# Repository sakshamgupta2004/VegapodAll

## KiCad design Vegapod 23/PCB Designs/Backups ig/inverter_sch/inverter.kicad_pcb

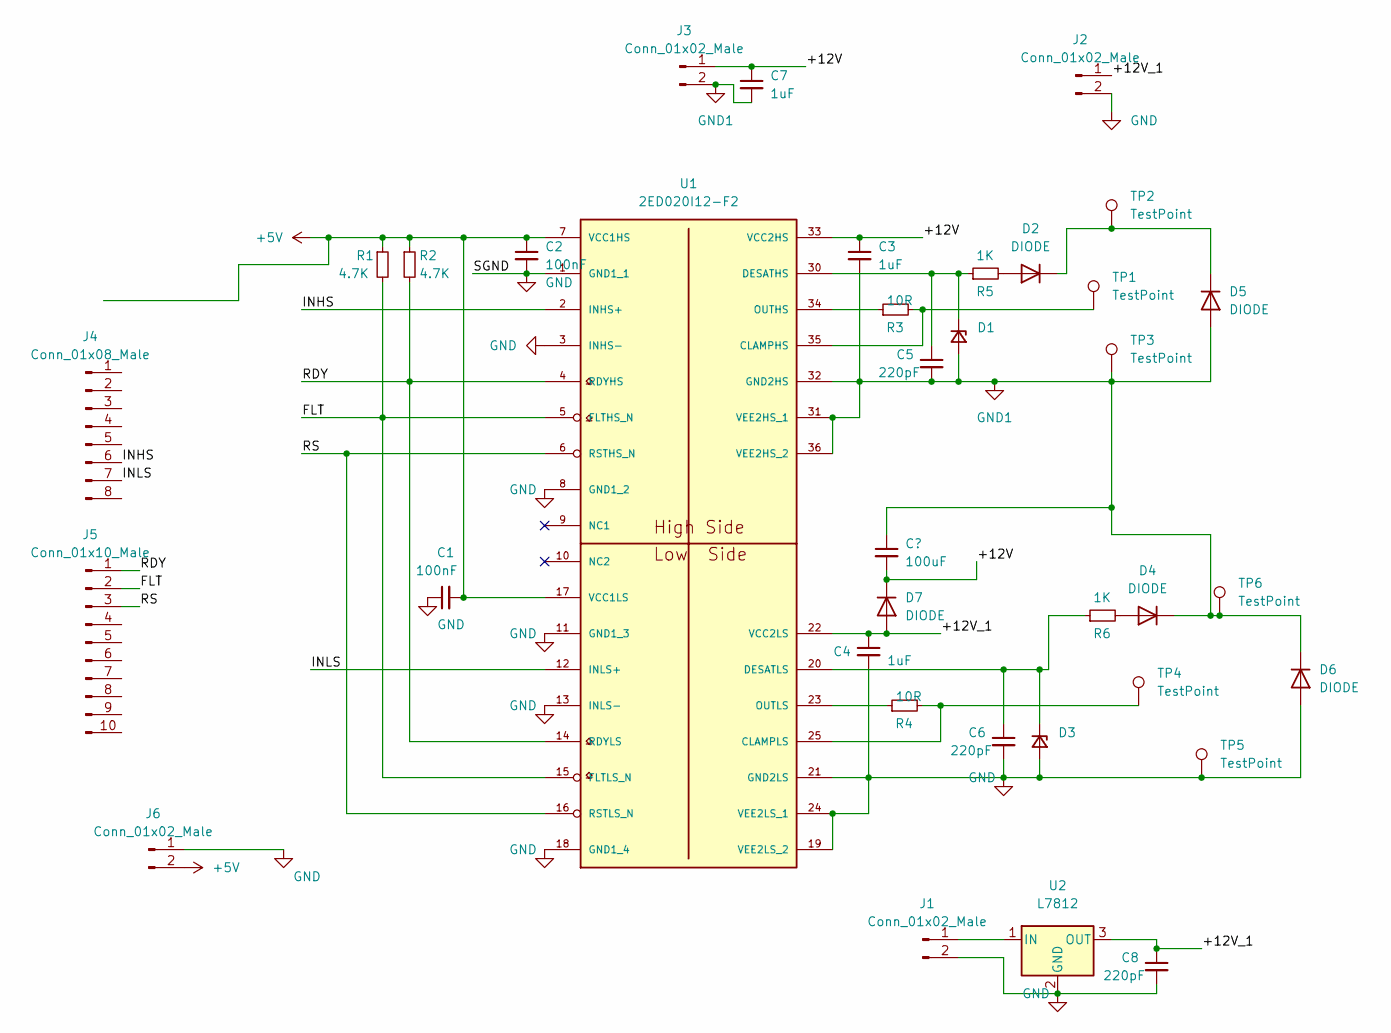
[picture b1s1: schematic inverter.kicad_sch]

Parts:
C1, C2: 100nF; CP_Radial_D14.0mm_P5.00mm
C3, C4, C7: 1uF; CP_Radial_D14.0mm_P5.00mm
C5, C6, C8: 220pF; CP_Radial_D14.0mm_P5.00mm
D1, D3: D_Zener_Small; D_DO-27_P15.24mm_Horizontal
D2, D4, D5, D6, D7: DIODE; D_DO-27_P15.24mm_Horizontal
J1, J2, J3: Conn_01x02_Male; PhoenixContact_MCV_1,5_2-G-5.08_1x02_P5.08mm_Vertical
J4: Conn_01x08_Male; PinHeader_1x08_P2.54mm_Vertical
J5: Conn_01x10_Male; PinHeader_1x10_P2.54mm_Vertical
J6: Conn_01x02_Male; PinHeader_1x02_P2.54mm_Vertical
R1, R2: 4.7K; R_Axial_DIN0411_L9.9mm_D3.6mm_P12.70mm_Horizontal
R3, R4: 10R; R_Axial_DIN0411_L9.9mm_D3.6mm_P12.70mm_Horizontal
R5, R6: 1K; R_Axial_DIN0411_L9.9mm_D3.6mm_P12.70mm_Horizontal
TP1, TP2, TP3, TP4, TP5, TP6: TestPoint; TestPoint_Pad_D4.0mm
U1: 2ED020I12-F2; SOP65P1030X265-36_32N-V
U2: L7812; TO-220-3_Vertical

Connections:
+5V: C1.2, C2.1, J6.2, R1.1, R2.1, U1.7 (VCC1HS), U1.17 (VCC1LS)
/+12V: C3.1, C7.1, D7.2 (K), J3.1, U1.33 (VCC2HS)
/+12V_1: C4.1, C8.1, D7.1 (A), J2.1, U1.22 (VCC2LS), U2.3 (OUT)
/FLT: J5.2, R1.2, U1.5 (FLTHS_N), U1.15 (FLTLS_N)
/INHS: J4.6, U1.2 (INHS+)
/INLS: J4.7, U1.12 (INLS+)
/RDY: J5.1, R2.2, U1.4 (RDYHS), U1.14 (RDYLS)
/RS: J5.3, U1.6 (RSTHS_N), U1.16 (RSTLS_N)
GND: C1.1, C2.2, C4.2, C6.2, C8.2, D3.2 (A), D6.1 (A), J1.2, J2.2, J6.1, TP5.1, U1.1 (GND1_1), U1.3 (INHS-), U1.8 (GND1_2), U1.11 (GND1_3), U1.13 (INLS-), U1.18 (GND1_4), U1.19 (VEE2LS_2), U1.21 (GND2LS), U1.24 (VEE2LS_1), U2.2 (GND)
GND1: C3.2, C5.2, C7.2, D1.2 (A), D4.2 (K), D5.1 (A), D6.2 (K), J3.2, TP3.1, TP6.1, U1.31 (VEE2HS_1), U1.32 (GND2HS), U1.36 (VEE2HS_2)
unnamed: C5.1, D1.1 (K), R5.1, U1.30 (DESATHS)
unnamed: C6.1, D3.1 (K), R6.1, U1.20 (DESATLS)
unnamed: D2.1 (A), R5.2
unnamed: D2.2 (K), D5.2 (K), TP2.1
unnamed: D4.1 (A), R6.2
unnamed: J1.1, U2.1 (IN)
unnamed: R3.1, U1.34 (OUTHS)
unnamed: R3.2, TP1.1, U1.35 (CLAMPHS)
unnamed: R4.1, U1.23 (OUTLS)
unnamed: R4.2, TP4.1, U1.25 (CLAMPLS)

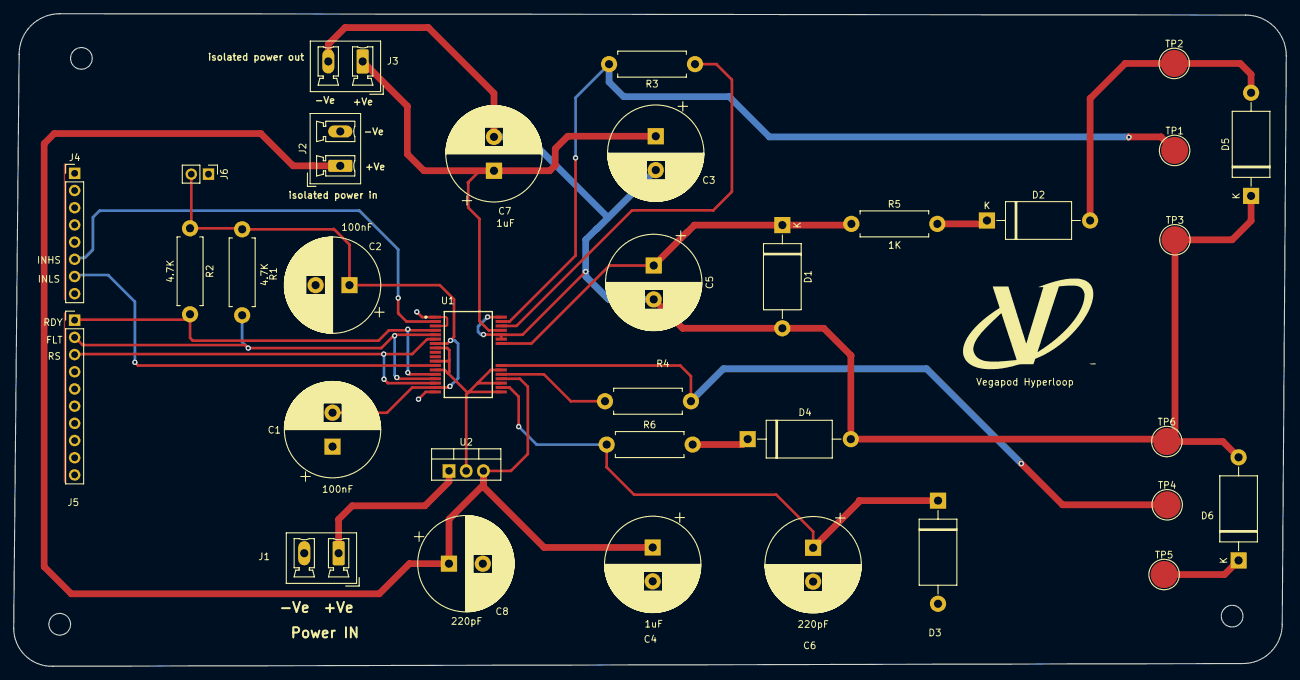
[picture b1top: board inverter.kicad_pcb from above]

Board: 2 copper layers, 188.0 x 96.4 mm, 34 parts (0 on the bottom side), 20 nets.

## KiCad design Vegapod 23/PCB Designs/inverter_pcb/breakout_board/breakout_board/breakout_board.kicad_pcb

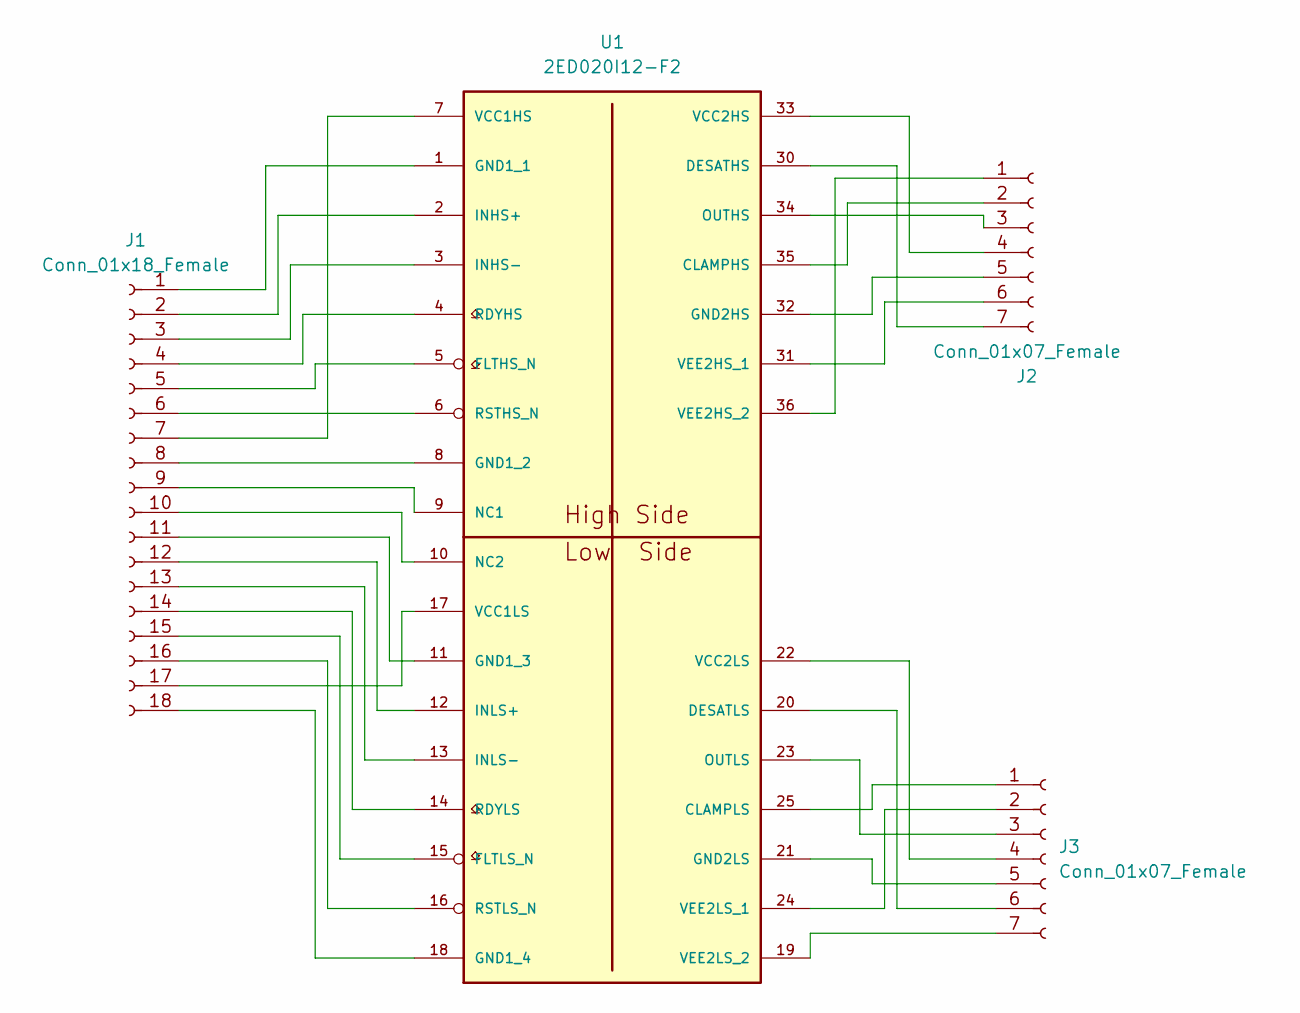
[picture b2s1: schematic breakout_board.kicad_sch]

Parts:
J1: Conn_01x18_Female; PinSocket_1x18_P2.54mm_Vertical
J2, J3: Conn_01x07_Female; PinSocket_1x07_P2.54mm_Vertical
U1: 2ED020I12-F2; SOP65P1030X265-36_32N-V

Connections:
unnamed: J1.1, U1.1 (GND1_1)
unnamed: J1.2, U1.2 (INHS+)
unnamed: J1.3, U1.3 (INHS-)
unnamed: J1.4, U1.4 (RDYHS)
unnamed: J1.5, U1.5 (FLTHS_N)
unnamed: J1.6, U1.6 (RSTHS_N)
unnamed: J1.7, U1.7 (VCC1HS)
unnamed: J1.8, U1.8 (GND1_2)
unnamed: J1.9, U1.9 (NC1)
unnamed: J1.10, U1.10 (NC2)
unnamed: J1.11, U1.11 (GND1_3)
unnamed: J1.12, U1.12 (INLS+)
unnamed: J1.13, U1.13 (INLS-)
unnamed: J1.14, U1.14 (RDYLS)
unnamed: J1.15, U1.15 (FLTLS_N)
unnamed: J1.16, U1.16 (RSTLS_N)
unnamed: J1.17, U1.17 (VCC1LS)
unnamed: J1.18, U1.18 (GND1_4)
unnamed: J2.1, U1.36 (VEE2HS_2)
unnamed: J2.2, U1.35 (CLAMPHS)
unnamed: J2.3, U1.34 (OUTHS)
unnamed: J2.4, U1.33 (VCC2HS)
unnamed: J2.5, U1.32 (GND2HS)
unnamed: J2.6, U1.31 (VEE2HS_1)
unnamed: J2.7, U1.30 (DESATHS)
unnamed: J3.1, U1.25 (CLAMPLS)
unnamed: J3.2, U1.24 (VEE2LS_1)
unnamed: J3.3, U1.23 (OUTLS)
unnamed: J3.4, U1.22 (VCC2LS)
unnamed: J3.5, U1.21 (GND2LS)
unnamed: J3.6, U1.20 (DESATLS)
unnamed: J3.7, U1.19 (VEE2LS_2)

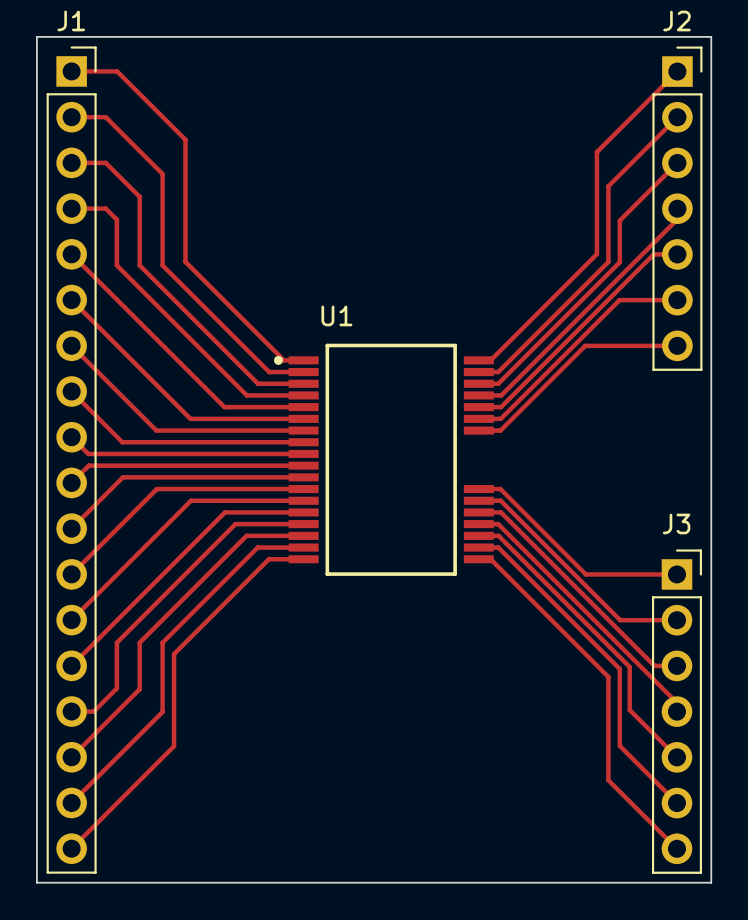
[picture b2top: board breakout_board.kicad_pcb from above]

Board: 2 copper layers, 37.5 x 47.0 mm, 4 parts (0 on the bottom side), 32 nets.

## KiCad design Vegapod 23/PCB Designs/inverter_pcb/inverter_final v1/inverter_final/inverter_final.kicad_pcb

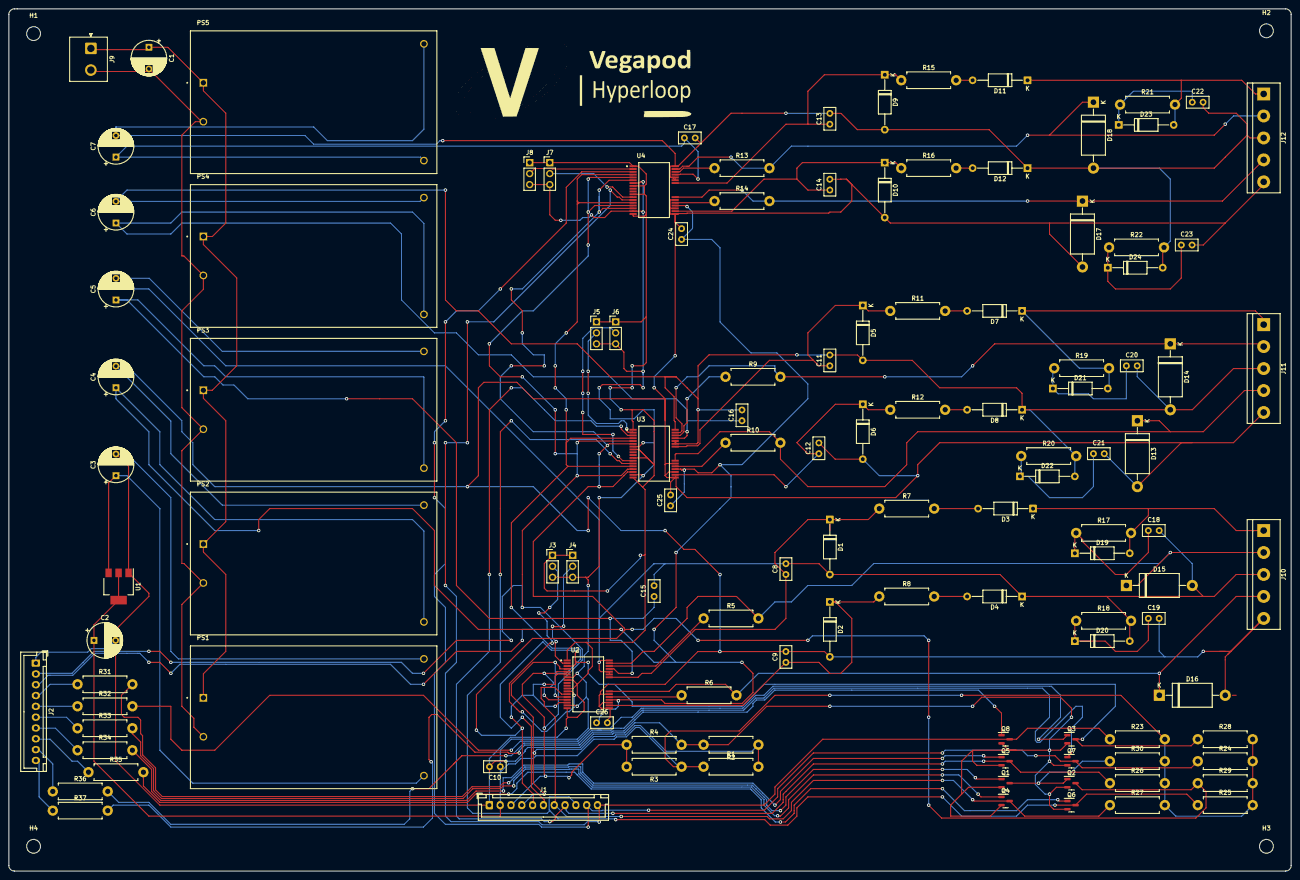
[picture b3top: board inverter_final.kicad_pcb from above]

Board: 2 copper layers, 296.5 x 199.4 mm, 120 parts (0 on the bottom side), 76 nets.

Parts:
C1: 100uF; CP_Radial_D8.0mm_P5.00mm
C2, C3, C4, C5, C6, C7: 1000uF; CP_Radial_D8.0mm_P5.00mm
C8, C9, C11, C12, C13, C14: 220pF; C_Disc_D5.0mm_W2.5mm_P2.50mm
C10, C15, C16, C17, C24, C25, C26: 100nF; C_Disc_D5.0mm_W2.5mm_P2.50mm
C18, C19, C20, C21, C22, C23: C_Snub; C_Disc_D5.0mm_W2.5mm_P2.50mm
D1, D2, D5, D6, D9, D10: D_Schottky; D_A-405_P12.70mm_Horizontal
D3, D4, D7, D8, D11, D12: 1N4007; D_A-405_P12.70mm_Horizontal
D13, D14, D15, D16, D17, D18: D_Zener; D_DO-201AE_P15.24mm_Horizontal
D19, D20, D21, D22, D23, D24: D_Snub; D_A-405_P12.70mm_Horizontal
H1, H2, H3, H4: MountingHole; MountingHole_3.2mm_M3
J1: Conn_01x11_Male; JST_XH_B11B-XH-A_1x11_P2.50mm_Vertical
J2: Conn_01x10_Male; JST_XH_B10B-XH-A_1x10_P2.50mm_Vertical
J3, J4, J5, J6, J7, J8: Conn_01x03_Male; PinHeader_1x03_P2.54mm_Vertical
J9: Conn_01x02_Male; JST_NV_B02P-NV_1x02_P5.00mm_Vertical
J10, J11, J12: Screw_Terminal_01x05; TerminalBlock_bornier-5_P5.08mm
PS1, PS2, PS3, PS4, PS5: HLK-20M05; CONV_HLK-20M05
Q1, Q2, Q3, Q4, Q5, Q6, Q7, Q8: MMBT3904; SOT-23
R1, R3: 3.3K; R_Axial_DIN0411_L9.9mm_D3.6mm_P12.70mm_Horizontal
R2, R4: 4.7K; R_Axial_DIN0411_L9.9mm_D3.6mm_P12.70mm_Horizontal
R5, R6, R9, R10, R13, R14: 10; R_Axial_DIN0411_L9.9mm_D3.6mm_P12.70mm_Horizontal
R7, R8, R11, R12, R15, R16, R23, R24, R25, R26, R27, R28, R29, R30, R31, R32, R33, R34, R35, R36, R37: 1K; R_Axial_DIN0411_L9.9mm_D3.6mm_P12.70mm_Horizontal
R17, R18, R19, R20, R21, R22: R_Snub; R_Axial_DIN0411_L9.9mm_D3.6mm_P12.70mm_Horizontal
U1: AMS1117-5.0; SOT-223-3_TabPin2
U2, U3, U4: 2ED020I12-F2; SOP65P1030X265-36_32N-V

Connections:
+5V: C2.1, C10.1, J1.2, J3.3, J4.3, J5.3, J6.3, J7.3, J8.3, R1.1, R3.1, R23.2, R24.2, R25.2, R26.2, R27.2, R28.2, R29.2, R30.2, U1.2 (VO), U2.7 (VCC1HS), U2.17 (VCC1LS), U3.7 (VCC1HS), U3.17 (VCC1LS), U4.7 (VCC1HS), U4.17 (VCC1LS)
+15V: C4.1, C24.1, C25.1, C26.1, PS2.4 (+VO), U2.22 (VCC2LS), U3.22 (VCC2LS), U4.22 (VCC2LS)
+BATT: C1.1, J9.1, PS1.1 (AC(L)), PS2.1 (AC(L)), PS3.1 (AC(L)), PS4.1 (AC(L)), PS5.1 (AC(L))
-BATT: C1.2, J9.2, PS1.2 (AC(N)), PS2.2 (AC(N)), PS3.2 (AC(N)), PS4.2 (AC(N)), PS5.2 (AC(N))
FLT: J1.3, J2.2, R3.2, R4.1, U2.5 (FLTHS_N), U2.15 (FLTLS_N), U3.5 (FLTHS_N), U3.15 (FLTLS_N), U4.5 (FLTHS_N), U4.15 (FLTLS_N)
GND: C4.2, C9.2, C12.2, C14.2, C19.2, C21.2, C23.2, C24.2, C25.2, C26.2, D2.2 (A), D6.2 (A), D10.2 (A), D13.2 (A), D16.2 (A), D17.2 (A), J10.5, J11.5, J12.5, PS2.3 (-VO), U2.19 (VEE2LS_2), U2.21 (GND2LS), U2.24 (VEE2LS_1), U3.19 (VEE2LS_2), U3.21 (GND2LS), U3.24 (VEE2LS_1), U4.19 (VEE2LS_2), U4.21 (GND2LS), U4.24 (VEE2LS_1)
GND1: C5.2, C8.2, C15.2, C18.2, D1.2 (A), D4.1 (K), D15.2 (A), D20.2 (A), J10.3, PS3.3 (-VO), R18.2, U2.31 (VEE2HS_1), U2.32 (GND2HS), U2.36 (VEE2HS_2)
GND2: C6.2, C11.2, C16.2, C20.2, D5.2 (A), D8.1 (K), D14.2 (A), D22.2 (A), J11.3, PS4.3 (-VO), R20.2, U3.31 (VEE2HS_1), U3.32 (GND2HS), U3.36 (VEE2HS_2)
GND3: C7.2, C13.2, C17.2, C22.2, D9.2 (A), D12.1 (K), D18.2 (A), D24.2 (A), J12.3, PS5.3 (-VO), R22.2, U4.31 (VEE2HS_1), U4.32 (GND2HS), U4.36 (VEE2HS_2)
GNDD: C2.2, C3.2, C10.2, J1.1, J2.1, J3.1, J4.1, J5.1, J6.1, J7.1, J8.1, PS1.3 (-VO), Q1.2 (E), Q2.2 (E), Q3.2 (E), Q4.2 (E), Q5.2 (E), Q6.2 (E), Q7.2 (E), Q8.2 (E), R2.2, R4.2, U1.1 (GND), U2.1 (GND1_1), U2.8 (GND1_2), U2.11 (GND1_3), U2.18 (GND1_4), U3.1 (GND1_1), U3.8 (GND1_2), U3.11 (GND1_3), U3.18 (GND1_4), U4.1 (GND1_1), U4.8 (GND1_2), U4.11 (GND1_3), U4.18 (GND1_4)
INHS1: J1.6, Q3.3 (C), R28.1, U2.3 (INHS-)
INHS2: J1.8, Q5.3 (C), R26.1, U3.3 (INHS-)
INHS3: J1.10, Q7.3 (C), R24.1, U4.3 (INHS-)
INLS1: J1.7, Q4.3 (C), R27.1, U2.13 (INLS-)
INLS2: J1.9, Q6.3 (C), R25.1, U3.13 (INLS-)
INLS3: J1.11, Q8.3 (C), R23.1, U4.13 (INLS-)
unnamed: C8.1, D1.1 (K), R7.1, U2.30 (DESATHS)
unnamed: C9.1, D2.1 (K), R8.1, U2.20 (DESATLS)
unnamed: C11.1, D5.1 (K), R11.1, U3.30 (DESATHS)
unnamed: C12.1, D6.1 (K), R12.1, U3.20 (DESATLS)
unnamed: C13.1, D9.1 (K), R15.1, U4.30 (DESATHS)
unnamed: C14.1, D10.1 (K), R16.1, U4.20 (DESATLS)
unnamed: C18.1, D19.1 (K), R17.1
unnamed: C19.1, D20.1 (K), R18.1
unnamed: C20.1, D21.1 (K), R19.1
unnamed: C21.1, D22.1 (K), R20.1
unnamed: C22.1, D23.1 (K), R21.1
unnamed: C23.1, D24.1 (K), R22.1
unnamed: D3.2 (A), R7.2
unnamed: D4.2 (A), R8.2
unnamed: D7.2 (A), R11.2
unnamed: D8.2 (A), R12.2
unnamed: D11.1 (K), D23.2 (A), J12.1, R21.2
unnamed: D11.2 (A), R15.2
unnamed: D12.2 (A), R16.2
unnamed: D13.1 (K), J11.4, R10.2, U3.25 (CLAMPLS)
unnamed: D14.1 (K), J11.2, R9.2, U3.35 (CLAMPHS)
unnamed: D15.1 (K), J10.2, R5.2, U2.35 (CLAMPHS)
unnamed: D16.1 (K), J10.4, R6.2, U2.25 (CLAMPLS)
unnamed: D17.1 (K), J12.4, R14.2, U4.25 (CLAMPLS)
unnamed: D18.1 (K), J12.2, R13.2, U4.35 (CLAMPHS)
unnamed: D3.1 (K), D19.2 (A), J10.1, R17.2
unnamed: D7.1 (K), D21.2 (A), J11.1, R19.2
unnamed: J2.4, R31.1
unnamed: J2.5, R32.1
unnamed: J2.6, R33.1
unnamed: J2.7, R34.1
unnamed: J2.8, R35.1
unnamed: J2.9, R36.1
unnamed: J2.10, R37.1
unnamed: J3.2, U2.12 (INLS+)
unnamed: J4.2, U2.2 (INHS+)
unnamed: J5.2, U3.2 (INHS+)
unnamed: J6.2, U3.12 (INLS+)
unnamed: J7.2, U4.12 (INLS+)
unnamed: J8.2, U4.2 (INHS+)
unnamed: Q1.1 (B), R31.2
unnamed: Q1.3 (C), Q2.1 (B), R30.1
unnamed: Q3.1 (B), R32.2
unnamed: Q4.1 (B), R33.2
unnamed: Q5.1 (B), R34.2
unnamed: Q6.1 (B), R35.2
unnamed: Q7.1 (B), R36.2
unnamed: Q8.1 (B), R37.2
unnamed: R5.1, U2.34 (OUTHS)
unnamed: R6.1, U2.23 (OUTLS)
unnamed: R9.1, U3.34 (OUTHS)
unnamed: R10.1, U3.23 (OUTLS)
unnamed: R13.1, U4.34 (OUTHS)
unnamed: R14.1, U4.23 (OUTLS)
RDY: J1.4, J2.3, R1.2, R2.1, U2.4 (RDYHS), U2.14 (RDYLS), U3.4 (RDYHS), U3.14 (RDYLS), U4.4 (RDYHS), U4.14 (RDYLS)
RST: J1.5, Q2.3 (C), R29.1, U2.6 (RSTHS_N), U2.16 (RSTLS_N), U3.6 (RSTHS_N), U3.16 (RSTLS_N), U4.6 (RSTHS_N), U4.16 (RSTLS_N)
VDD: C3.1, PS1.4 (+VO), U1.3 (VI)
VDrive1: C5.1, C15.1, PS3.4 (+VO), U2.33 (VCC2HS)
VDrive2: C6.1, C16.1, PS4.4 (+VO), U3.33 (VCC2HS)
VDrive3: C7.1, C17.1, PS5.4 (+VO), U4.33 (VCC2HS)

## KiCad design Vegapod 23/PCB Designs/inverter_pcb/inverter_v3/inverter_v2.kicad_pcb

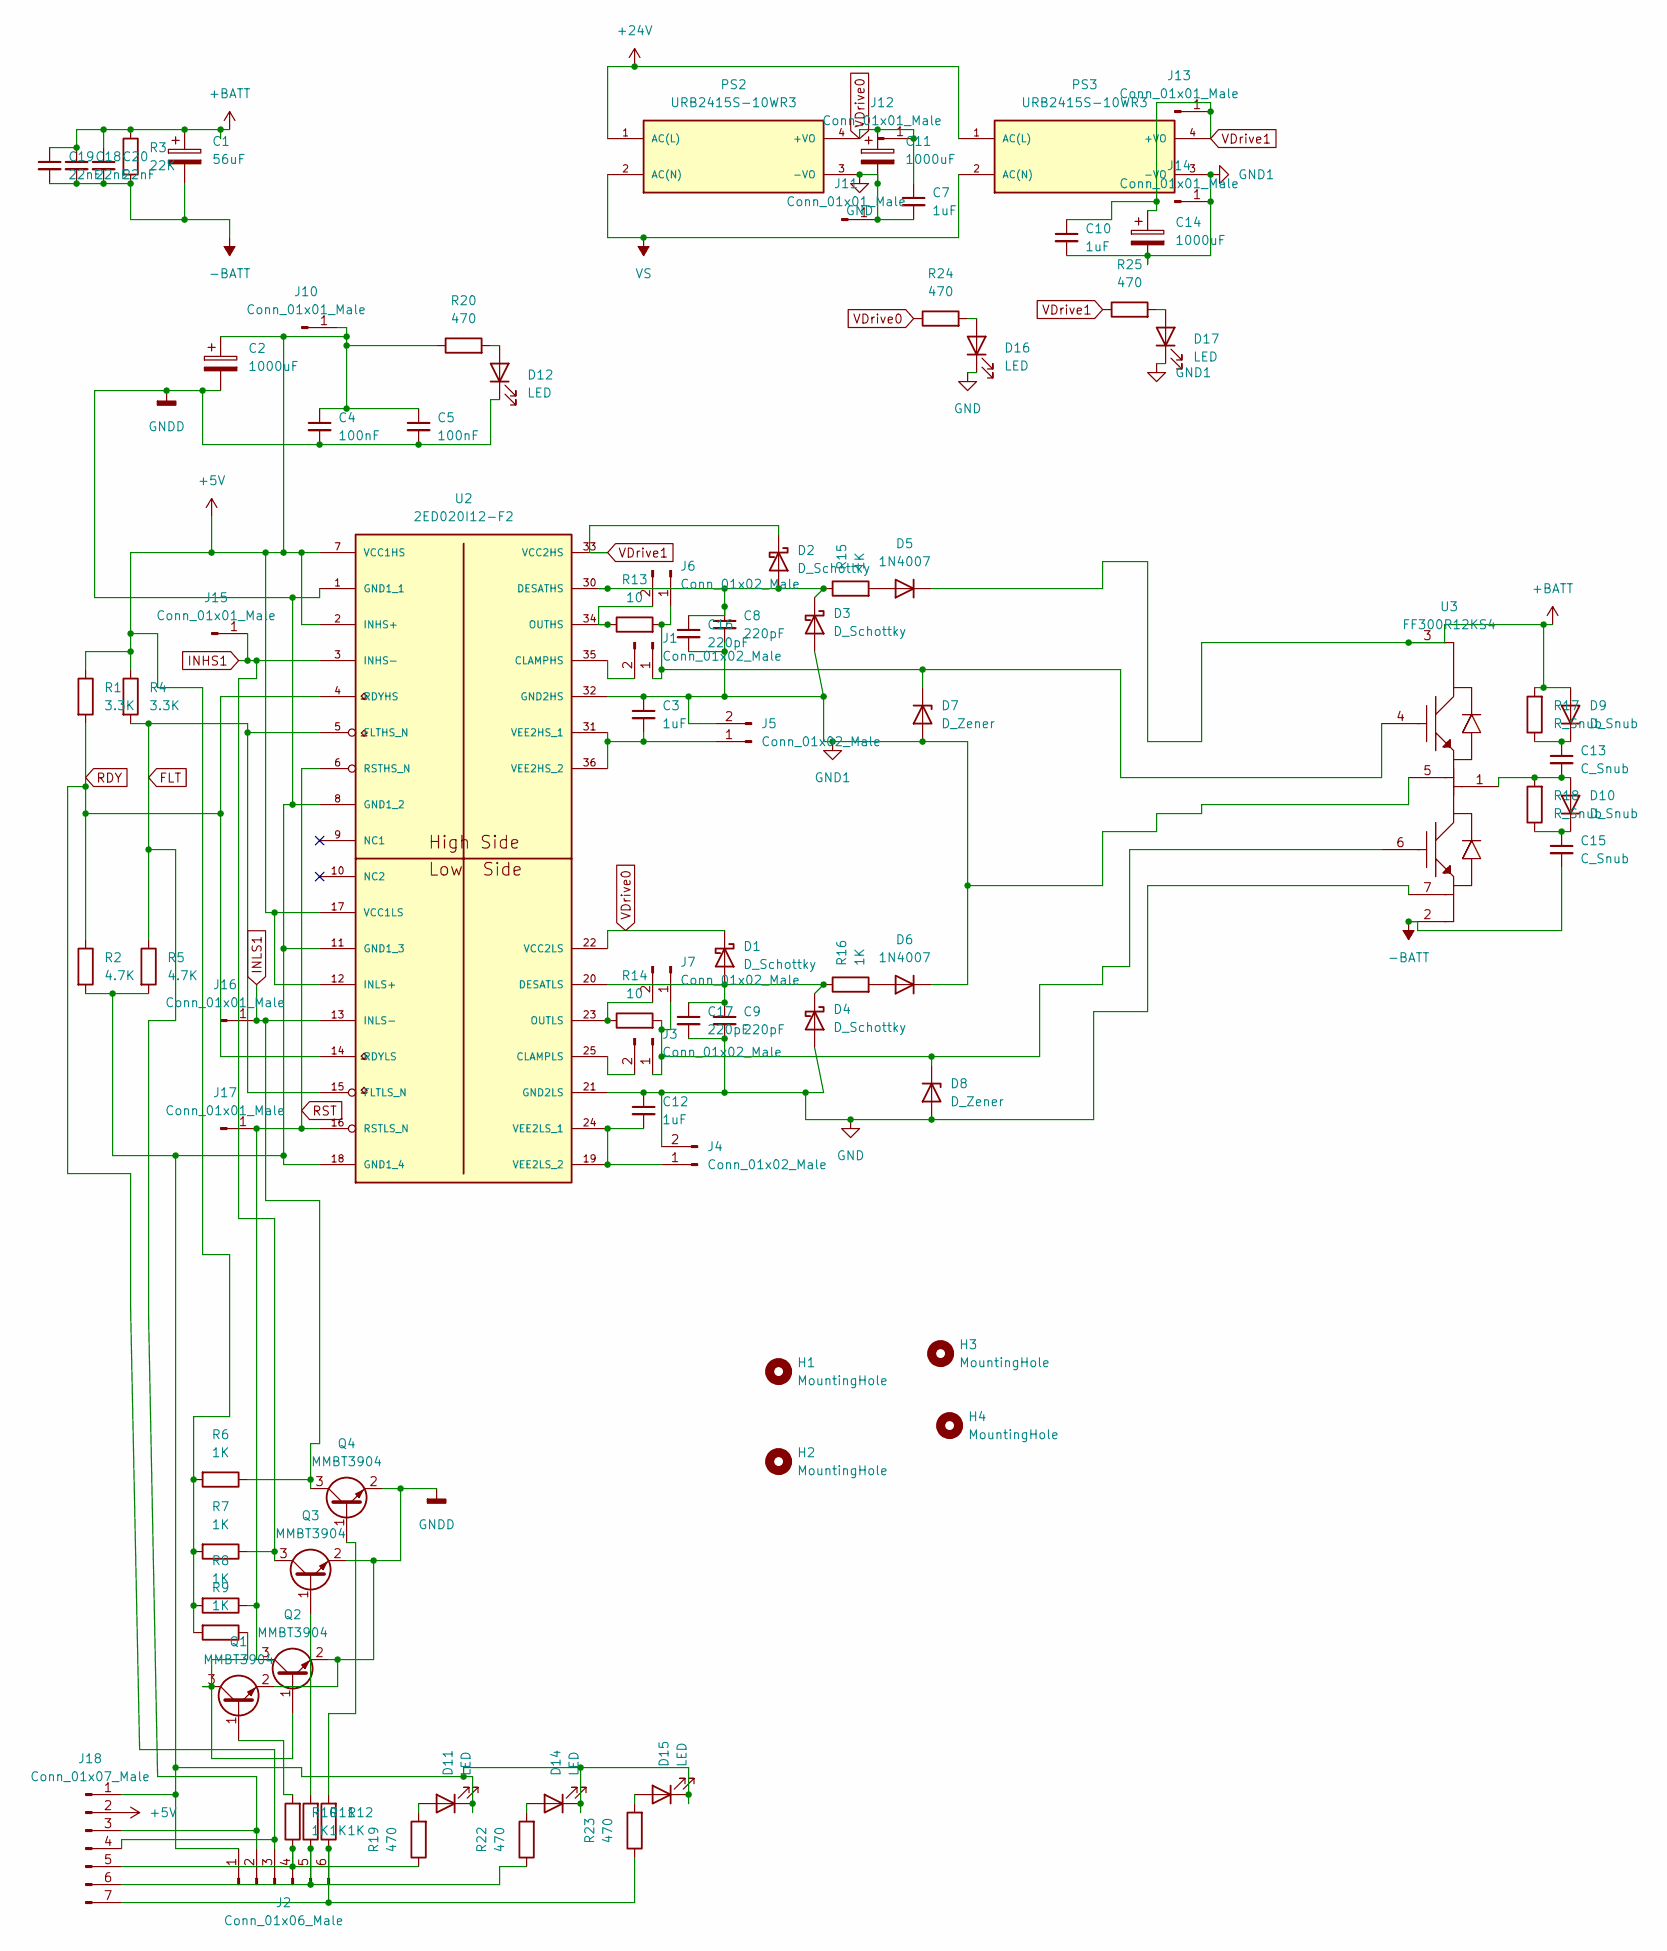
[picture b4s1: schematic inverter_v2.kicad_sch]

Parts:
C1: 56uF; CP_Radial_D16.0mm_P7.50mm
C2: 1000uF; CP_Elec_10x10.5
C3, C7, C10, C12: 1uF; C_1206_3216Metric_Pad1.33x1.80mm_HandSolder
C4, C5: 100nF; C_0603_1608Metric_Pad1.08x0.95mm_HandSolder
C8, C9, C16, C17: 220pF; C_0603_1608Metric_Pad1.08x0.95mm_HandSolder
C11, C14: 1000uF; CAP_EEEFK1E102AQ
C13, C15: C_Snub; C_Rect_L24.0mm_W8.3mm_P22.50mm_MKT
C18, C19, C20: 22nF; C_1206_3216Metric_Pad1.33x1.80mm_HandSolder
D1, D2, D3, D4: D_Schottky; D_SMA_Handsoldering
D5, D6: 1N4007; D_SMA_Handsoldering
D7, D8: D_Zener; D_SOD-123
D9, D10: D_Snub; D_DO-201AE_P15.24mm_Horizontal
D11, D12, D14, D15, D16, D17: LED; LED_0805_2012Metric_Pad1.15x1.40mm_HandSolder
H1, H2, H3, H4: MountingHole; MountingHole_3.2mm_M3
J1, J3, J4, J5, J6, J7: Conn_01x02_Male; PinHeader_1x02_P1.27mm_Vertical
J2: Conn_01x06_Male; JST_XH_B6B-XH-A_1x06_P2.50mm_Vertical
J10, J11, J12, J13, J14, J15, J16, J17: Conn_01x01_Male; PinHeader_1x01_P2.54mm_Vertical
J18: Conn_01x07_Male; JST_XH_B7B-XH-A_1x07_P2.50mm_Vertical
PS2, PS3: URB2415S-10WR3; CONV_HLK-20M05; PARTREV V1.3
Q1, Q2, Q3, Q4: MMBT3904; SOT-23
R1, R4: 3.3K; R_0603_1608Metric_Pad0.98x0.95mm_HandSolder
R2, R5: 4.7K; R_0603_1608Metric_Pad0.98x0.95mm_HandSolder
R3: 22K; R_1206_3216Metric_Pad1.30x1.75mm_HandSolder
R6, R7, R8, R9, R10, R11, R12, R15, R16: 1K; R_0603_1608Metric_Pad0.98x0.95mm_HandSolder
R13, R14: 10; R_1206_3216Metric_Pad1.30x1.75mm_HandSolder
R17, R18: R_Snub; R_Box_L26.0mm_W5.0mm_P20.00mm
R19, R20, R22, R23, R24, R25: 470; R_0603_1608Metric_Pad0.98x0.95mm_HandSolder
U2: 2ED020I12-F2; SOP65P1030X265-36_32N-V
U3: FF300R12KS4

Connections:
+5V: C2.1, C4.1, C5.1, J10.1, J18.2, R1.1, R4.1, R6.2, R7.2, R8.2, R9.2, R20.1, U2.2 (INHS+), U2.7 (VCC1HS), U2.12 (INLS+), U2.17 (VCC1LS); also elsewhere on the board
FLT: J2.2, J18.3, R4.2, R5.1, U2.5 (FLTHS_N), U2.15 (FLTLS_N)
GND: C7.2, C9.2, C11.2, C12.1, C17.2, D4.2 (A), D8.2 (A), D16.1 (K), J4.2, J11.1, PS2.3 (-VO), U2.21 (GND2LS), U3.7
GND1: C3.1, C8.2, C10.2, C14.2, C16.2, D3.2 (A), D6.1 (K), D7.2 (A), D17.1 (K), J5.2, J14.1, PS3.3 (-VO), U2.32 (GND2HS), U3.5
GNDD: C2.2, C4.2, C5.2, D11.1 (K), D12.1 (K), D14.1 (K), D15.1 (K), J2.1, J18.1, Q1.2 (E), Q2.2 (E), Q3.2 (E), Q4.2 (E), R2.2, R5.2, U2.1 (GND1_1), U2.8 (GND1_2), U2.11 (GND1_3), U2.18 (GND1_4); also elsewhere on the board
INHS1: J15.1, Q3.3 (C), R7.1, U2.3 (INHS-)
INLS1: J16.1, Q4.3 (C), R6.1, U2.13 (INLS-)
unnamed: C3.2, J5.1, U2.31 (VEE2HS_1), U2.36 (VEE2HS_2)
unnamed: C12.2, J4.1, U2.19 (VEE2LS_2), U2.24 (VEE2LS_1)
unnamed: C13.1, D9.1 (K), R17.1
unnamed: C13.2, D10.2 (A), R18.2, U3.1
unnamed: C15.1, D10.1 (K), R18.1
unnamed: C8.1, C16.1, D2.2 (A), D3.1 (K), R15.1, U2.30 (DESATHS)
unnamed: C9.1, C17.1, D1.2 (A), D4.1 (K), R16.1, U2.20 (DESATLS)
unnamed: D5.2 (A), R15.2
unnamed: D6.2 (A), R16.2
unnamed: D7.1 (K), J1.1, J6.1, R13.2, U3.4
unnamed: D8.1 (K), J3.1, J7.1, R14.2, U3.6
unnamed: D11.2 (A), R19.2
unnamed: D12.2 (A), R20.2
unnamed: D14.2 (A), R22.2
unnamed: D15.2 (A), R23.2
unnamed: D16.2 (A), R24.2
unnamed: D17.2 (A), R25.2
unnamed: J1.2, U2.35 (CLAMPHS)
unnamed: J3.2, U2.25 (CLAMPLS)
unnamed: J6.2, R13.1, U2.34 (OUTHS)
unnamed: J7.2, R14.1, U2.23 (OUTLS)
unnamed: J2.4, J18.5, R10.1, R19.1
unnamed: J2.5, J18.6, R11.1, R22.1
unnamed: J2.6, J18.7, R12.1, R23.1
unnamed: Q1.1 (B), R10.2
unnamed: Q1.3 (C), Q2.1 (B), R9.1
unnamed: Q3.1 (B), R11.2
unnamed: Q4.1 (B), R12.2
RDY: J2.3, J18.4, R1.2, R2.1, U2.4 (RDYHS), U2.14 (RDYLS)
RST: J17.1, Q2.3 (C), R8.1, U2.6 (RSTHS_N), U2.16 (RSTLS_N)
VDrive0: C7.1, C11.1, D1.1 (K), J12.1, PS2.4 (+VO), R24.1, U2.22 (VCC2LS)
VDrive1: C10.1, C14.1, D2.1 (K), J13.1, PS3.4 (+VO), R25.1, U2.33 (VCC2HS)

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
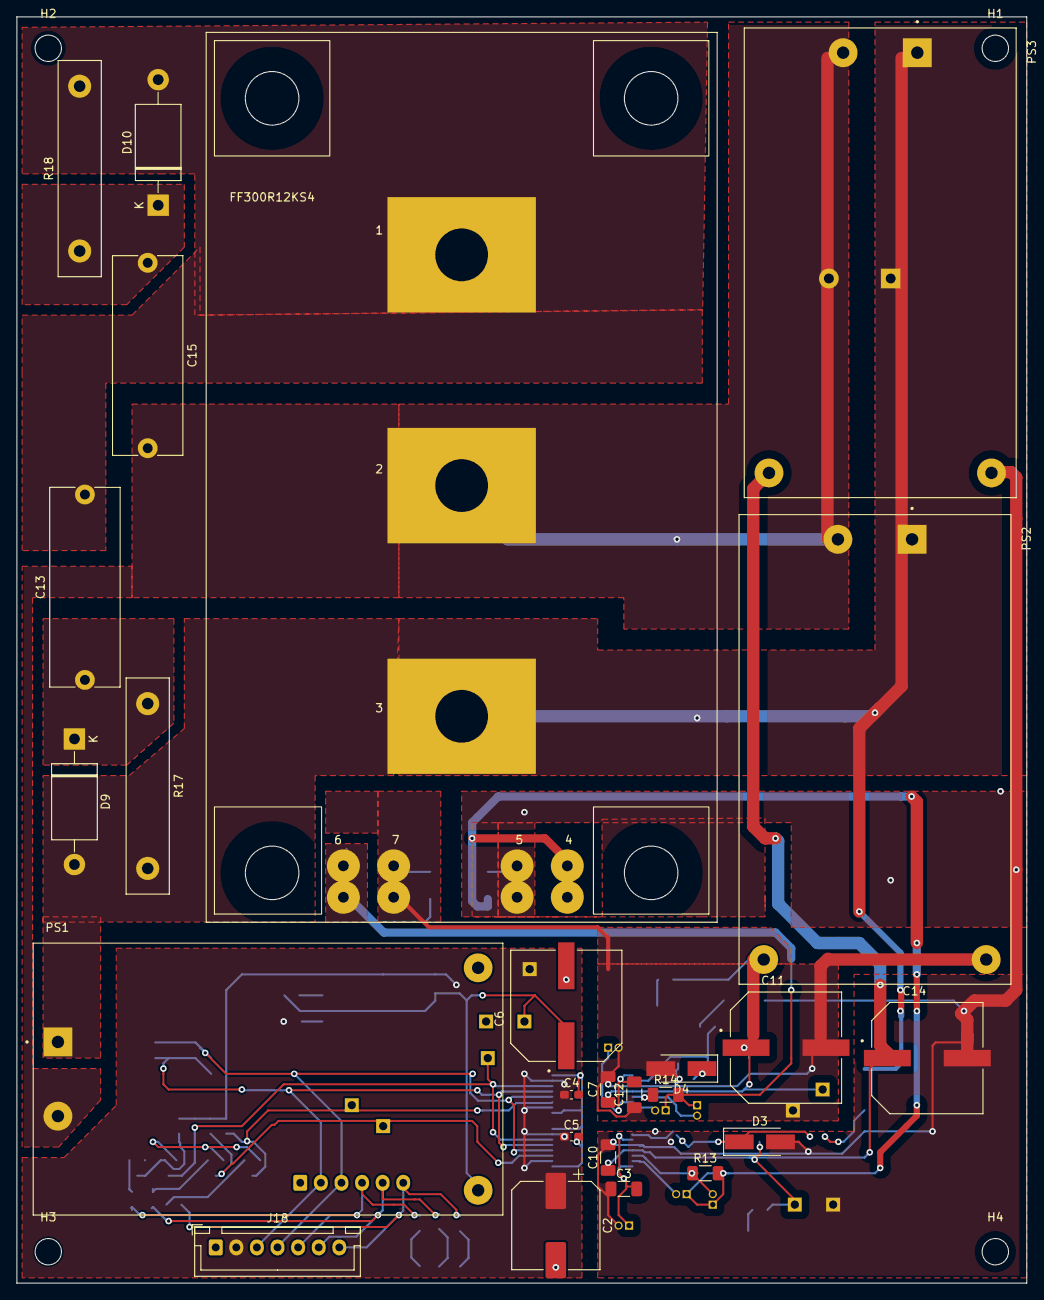
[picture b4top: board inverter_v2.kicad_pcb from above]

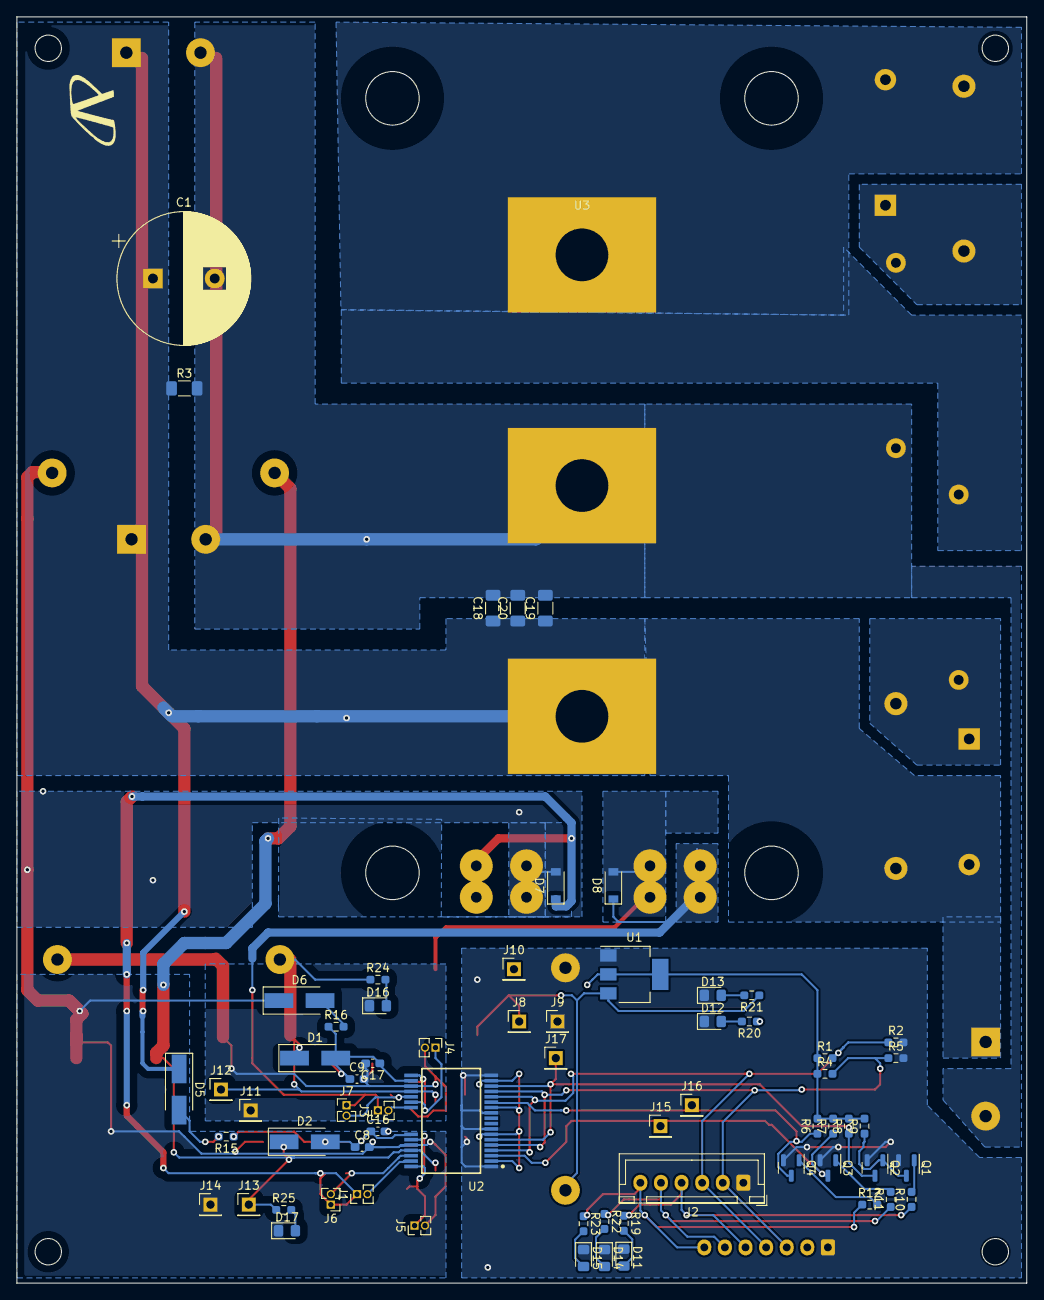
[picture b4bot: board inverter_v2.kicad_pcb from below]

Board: 2 copper layers, 122.6 x 153.7 mm, 94 parts (66 on the bottom side), 43 nets.

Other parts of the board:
C6: 1000uF; CAP_EEEFK1E102AQ
D13: LED; LED_0805_2012Metric_Pad1.15x1.40mm_HandSolder
J8, J9: Conn_01x01_Male; PinHeader_1x01_P2.54mm_Vertical
PS1: HLK-20M05; CONV_HLK-20M05
R21: 470; R_0603_1608Metric_Pad0.98x0.95mm_HandSolder
U1: AMS1117-5.0; SOT-223-3_TabPin2

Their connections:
+5V: U1.2 (VO); also elsewhere on the board
GNDD: C6.2, D13.1 (K), J9.1, PS1.3 (-VO), U1.1 (GND); also elsewhere on the board
unnamed: C6.1, J8.1, PS1.4 (+VO), R21.1, U1.3 (VI)
unnamed: D13.2 (A), R21.2
